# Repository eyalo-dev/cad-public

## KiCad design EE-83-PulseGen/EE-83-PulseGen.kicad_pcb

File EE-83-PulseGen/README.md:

Name:
- EE-83-PulseGen

Description:
- Pulse generator

Source reference:
- Everyday Electronics 1983-07 p.456 (58)

This is functional similar but not exact copy.
All dimension were estimated by eye.
Tried to use similar component placment as much as posible, but using only Kicad
standard PCB component footprint library, so dimentions may very.

PCB
- Done edit but
- Not tested

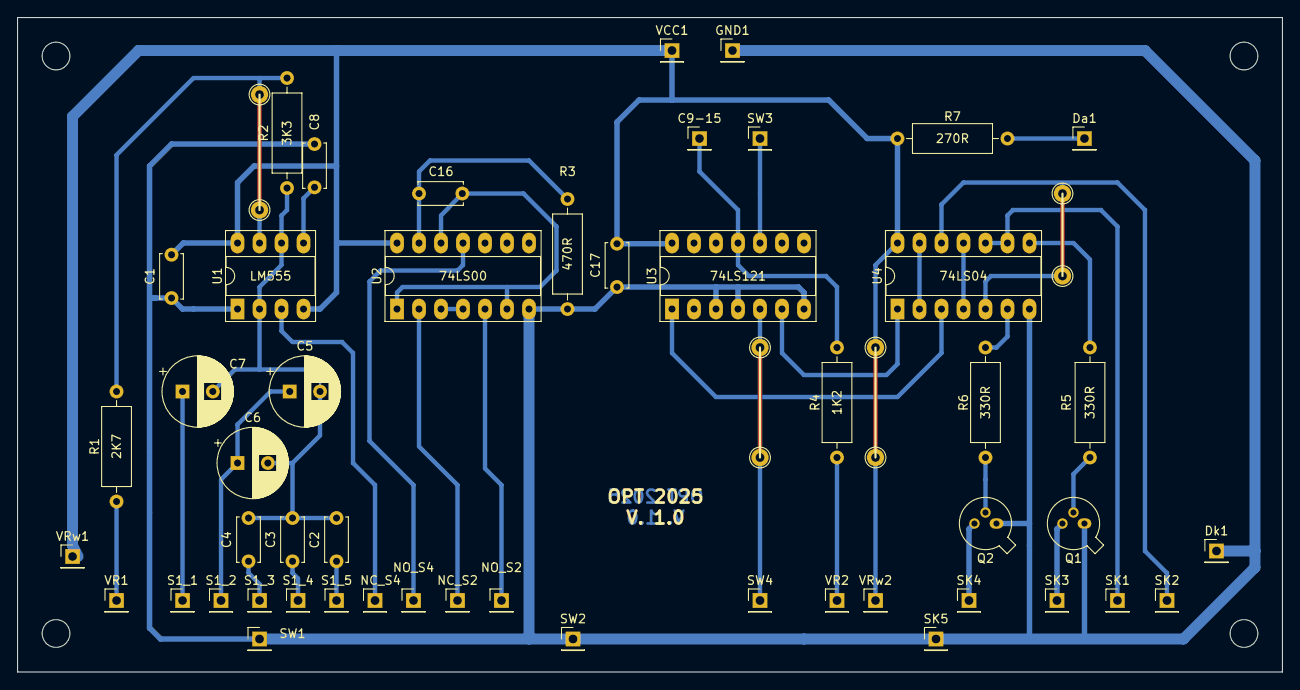
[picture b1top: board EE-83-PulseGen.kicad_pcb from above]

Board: 2 copper layers, 146.1 x 75.6 mm, 50 parts (0 on the bottom side), 35 nets.

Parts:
C1, C8, C17: 0.1uF; C_Disc_D5.0mm_W2.5mm_P5.00mm
C2, C16: 1nF; C_Disc_D5.0mm_W2.5mm_P5.00mm
C3: 15nF; C_Disc_D5.0mm_W2.5mm_P5.00mm
C4: 150nF; C_Disc_D5.0mm_W2.5mm_P5.00mm
C5: 1uF; CP_Radial_D8.0mm_P3.50mm
C6: 0.47uF; CP_Radial_D8.0mm_P3.50mm
C7: 15uF; CP_Radial_D8.0mm_P3.50mm
C9-15: PinHeader_1x01_P2.54mm_Vertical
Da1: PinHeader_1x01_P2.54mm_Vertical
Dk1: PinHeader_1x01_P2.54mm_Vertical
GND1: PinHeader_1x01_P2.54mm_Vertical
NC_S2, NC_S4: PinHeader_1x01_P2.54mm_Vertical
NO_S2, NO_S4: PinHeader_1x01_P2.54mm_Vertical
Q1, Q2: Q_NPN_EBC; TO-18-3
R1: 2K7; R_Axial_DIN0309_L9.0mm_D3.2mm_P12.70mm_Horizontal
R2: 3K3; R_Axial_DIN0309_L9.0mm_D3.2mm_P12.70mm_Horizontal
R3: 470R; R_Axial_DIN0309_L9.0mm_D3.2mm_P12.70mm_Horizontal
R4: 1K2; R_Axial_DIN0309_L9.0mm_D3.2mm_P12.70mm_Horizontal
R5, R6: 330R; R_Axial_DIN0309_L9.0mm_D3.2mm_P12.70mm_Horizontal
R7: 270R; R_Axial_DIN0309_L9.0mm_D3.2mm_P12.70mm_Horizontal
S1_1, S1_2, S1_3, S1_4, S1_5: PinHeader_1x01_P2.54mm_Vertical
SK1, SK2, SK3, SK4, SK5: PinHeader_1x01_P2.54mm_Vertical
SW1, SW2, SW3, SW4: PinHeader_1x01_P2.54mm_Vertical
U1: LM555; DIP-8_W7.62mm_Socket_LongPads
U2: 74LS00; DIP-14_W7.62mm_Socket_LongPads
U3: 74LS121; DIP-14_W7.62mm_Socket_LongPads
U4: 74LS04; DIP-14_W7.62mm_Socket_LongPads
VCC1: Conn_01x01_Female; PinHeader_1x01_P2.54mm_Vertical
VR1, VR2: PinHeader_1x01_P2.54mm_Vertical
VRw1, VRw2: PinHeader_1x01_P2.54mm_Vertical

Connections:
GNDREF: C1.1, C8.1, C17.1, Dk1.1, GND1.1, Q1.1, Q2.1, R3.1, SK5.1, SW1.1, SW2.1, U1.1, U2.7, U3.3, U3.4, U3.7, U4.7
unnamed: C2.1, C3.1, C4.1, C5.2, C6.2, C7.2, R2.1, U1.2, U1.6
unnamed: C2.2, S1_5.1
unnamed: C3.2, S1_4.1
unnamed: C4.2, S1_3.1
unnamed: C5.1, C6.1, S1_2.1
unnamed: C7.1, S1_1.1
unnamed: C8.2, U1.5
unnamed: C9-15.1, R4.1, U3.11
unnamed: C16.1, R3.2, U2.13
unnamed: C16.2, U2.1, U2.6, U2.12
unnamed: Da1.1, R7.1
unnamed: NC_S2.1, U2.2
unnamed: NC_S4.1, U1.3
unnamed: NO_S2.1, U2.5
unnamed: NO_S4.1, U2.11
unnamed: Q1.2, R5.1
unnamed: Q1.3, SK3.1
unnamed: Q2.2, R6.2
unnamed: Q2.3, SK4.1
unnamed: R1.1, R2.2, U1.7
unnamed: R1.2, VR1.1
unnamed: R4.2, VR2.1
unnamed: R5.2, U4.8
unnamed: R6.1, U4.6
unnamed: SW4.1, U3.5
unnamed: SK1.1, U4.9, U4.10
unnamed: SK2.1, U4.5, U4.12
unnamed: SW3.1, U3.10
unnamed: U2.3, U2.4
unnamed: U3.1, U4.3
unnamed: U3.6, U4.1
unnamed: U4.4, U4.11
unnamed: U4.2, U4.13
VCC: C1.2, C17.2, R7.2, U1.4, U1.8, U2.14, U3.14, U4.14, VCC1.1, VRw1.1, VRw2.1

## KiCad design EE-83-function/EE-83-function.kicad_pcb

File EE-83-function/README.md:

Name:
- EE-83-function

Description:
- Function generator

Source reference:
- Everyday Electronics 1983-04 p.14 (205)

This is functional similar but not exact copy.
All dimension were estimated by eye.
Tried to use similar component placment as much as posible, but using only Kicad
standard PCB component footprint library, so dimentions may very.

PCB
- Done edit but
- Not tested

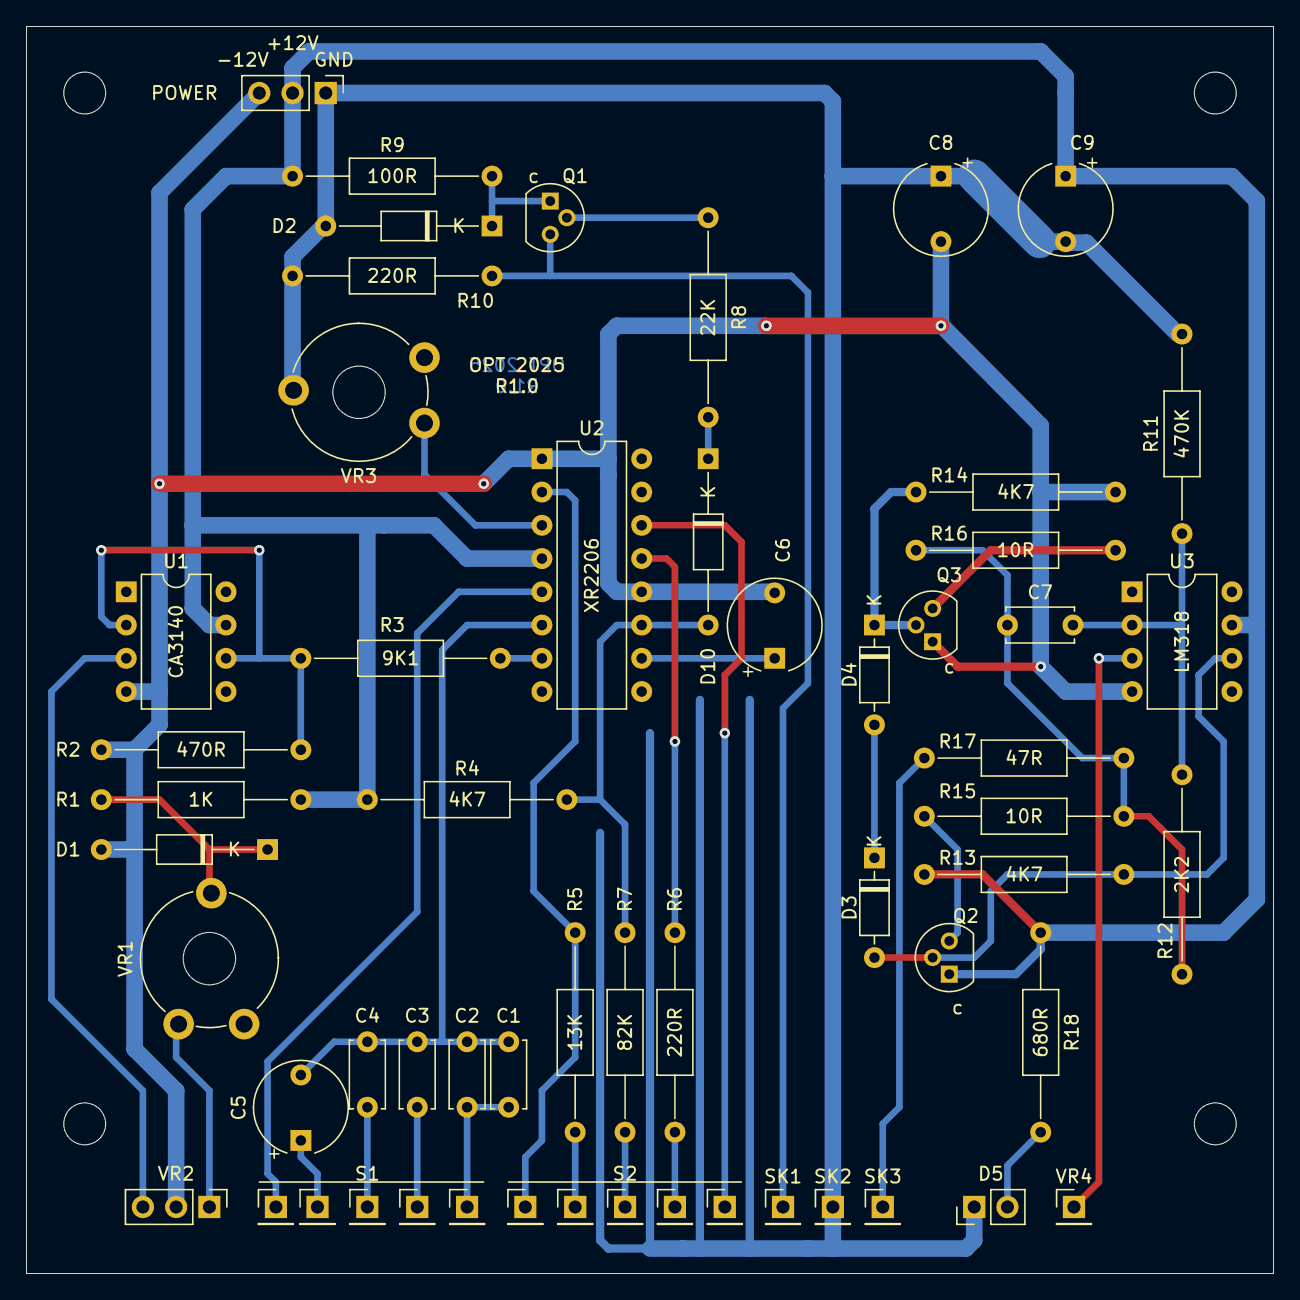
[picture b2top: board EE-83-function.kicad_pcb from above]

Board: 2 copper layers, 95.2 x 95.2 mm, 57 parts (0 on the bottom side), 37 nets.

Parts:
C1: 82p; C_Disc_D5.0mm_W2.5mm_P5.00mm
C2: 820p; C_Disc_D5.0mm_W2.5mm_P5.00mm
C3: 10n; C_Disc_D5.0mm_W2.5mm_P5.00mm
C4: 100n; C_Disc_D5.0mm_W2.5mm_P5.00mm
C5: 1u; CP_Radial_Tantal_D7.0mm_P5.00mm
C6, C8, C9: 22u; CP_Radial_Tantal_D7.0mm_P5.00mm
C7: 56p; C_Disc_D5.0mm_W2.5mm_P5.00mm
D1, D2, D10: D_DO-35_SOD27_P12.70mm_Horizontal
D3, D4: 1N4148; D_DO-35_SOD27_P7.62mm_Horizontal
D5: LED; PinHeader_1x02_P2.54mm_Vertical
POWER: 1K; PinHeader_1x03_P2.54mm_Vertical
Q1: BSX 20; TO-92
Q2: BC338; TO-92
Q3: BC328; TO-92
R1: 1K; R_Axial_DIN0207_L6.3mm_D2.5mm_P15.24mm_Horizontal
R2: 470R; R_Axial_DIN0207_L6.3mm_D2.5mm_P15.24mm_Horizontal
R3: 9K1; R_Axial_DIN0207_L6.3mm_D2.5mm_P15.24mm_Horizontal
R4, R13, R14: 4K7; R_Axial_DIN0207_L6.3mm_D2.5mm_P15.24mm_Horizontal
R5: 13K; R_Axial_DIN0207_L6.3mm_D2.5mm_P15.24mm_Horizontal
R6, R10: 220R; R_Axial_DIN0207_L6.3mm_D2.5mm_P15.24mm_Horizontal
R7: 82K; R_Axial_DIN0207_L6.3mm_D2.5mm_P15.24mm_Horizontal
R8: 22K; R_Axial_DIN0207_L6.3mm_D2.5mm_P15.24mm_Horizontal
R9: 100R; R_Axial_DIN0207_L6.3mm_D2.5mm_P15.24mm_Horizontal
R11: 470K; R_Axial_DIN0207_L6.3mm_D2.5mm_P15.24mm_Horizontal
R12: 2K2; R_Axial_DIN0207_L6.3mm_D2.5mm_P15.24mm_Horizontal
R15, R16: 10R; R_Axial_DIN0207_L6.3mm_D2.5mm_P15.24mm_Horizontal
R17: 47R; R_Axial_DIN0207_L6.3mm_D2.5mm_P15.24mm_Horizontal
R18: 680R; R_Axial_DIN0207_L6.3mm_D2.5mm_P15.24mm_Horizontal
S1, S2: Conn_01x01_Female; PinHeader_1x01_P2.54mm_Vertical
SK1, SK1#2, SK1#3, SK1#4, SK1#5, SK1#6, SK1#7, SK1#8, SK1#9, SK2, SK3: Conn_01x01_Female; PinHeader_1x01_P2.54mm_Vertical
U1: CA3140; DIP-8_W7.62mm
U2: XR2206; DIP-16_W7.62mm
U3: LM318; DIP-8_W7.62mm
VR1: 2K2; Potentiometer_Piher_PT-10-V10_Vertical_Hole
VR2: 1K; PinHeader_1x03_P2.54mm_Vertical
VR3: 47K; Potentiometer_Piher_PT-10-V10_Vertical_Hole
VR4: Conn_01x01_Female; PinHeader_1x01_P2.54mm_Vertical

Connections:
+12V: C9.1, POWER.2, Q2.1, R1.1, R4.1, R9.1, R13.1, R18.1, U1.7, U2.4, U3.7
-12V: C6.2, C8.2, D1.2, POWER.3, Q3.1, R2.1, R14.2, U1.4, U2.1, U2.12, U3.4, VR2.2
GND: C8.1, C9.2, D2.2, D5.1, POWER.1, R10.2, R11.2, SK2.1, VR3.2
unnamed: C1.1, C2.1, SK1#4.1
unnamed: C1.2, C2.2, C3.2, C4.2, C5.2, U2.6
unnamed: C3.1, SK1#3.1
unnamed: C4.1, S1.1
unnamed: C5.1, SK1#2.1
unnamed: C6.1, U2.10
unnamed: C7.1, R12.1, R15.2, R16.1, R17.2
unnamed: C7.2, R11.1, R12.2, U3.2
unnamed: D1.1, R1.2, VR1.1, VR1.2
unnamed: D2.1, Q1.1, R9.2
unnamed: D3.1, D4.2
unnamed: D3.2, Q2.2, R13.2, U3.6
unnamed: D4.1, Q3.2, R14.1
unnamed: D5.2, R18.2
unnamed: D10.1, R4.2, R7.2, U2.11
unnamed: D10.2, R8.2
unnamed: Q1.2, R8.1
unnamed: Q1.3, R10.1, SK1#9.1
unnamed: Q2.3, R15.1
unnamed: Q3.3, R16.2
unnamed: R2.2, R3.2, U1.2, U1.6
unnamed: R3.1, U2.7
unnamed: R5.1, SK1#7.1
unnamed: R5.2, SK1#8.1, U2.2
unnamed: R6.1, SK1#6.1
unnamed: R6.2, U2.13
unnamed: R7.1, S2.1
unnamed: R17.1, SK3.1
unnamed: SK1.1, U2.5
unnamed: SK1#5.1, U2.14
unnamed: U1.3, VR2.3
unnamed: U2.3, VR3.3
unnamed: U3.3, VR4.1
unnamed: VR1.3, VR2.1

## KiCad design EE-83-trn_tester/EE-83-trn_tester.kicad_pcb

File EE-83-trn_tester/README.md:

Name:
- EE-83-trn_tester

Description:
- Transistor and Diode Tester

Source reference:
- Everyday Electronics 1983-06 p.370 (44)

This is functional similar but not exact copy.
All dimension were estimated by eye.
Tried to use similar component placment as much as posible, but using only Kicad
standard PCB component footprint library, so dimentions may very.

Need to verify measurement of meter contacts for vertical mounting, like artical.

Two versions:
- 1 my failed attempt to make PCB width smaller - fit within the 100mm X 100mm limit.
- 2 this is sized similar to original. 

PCB
- Done edit but
- Not tested

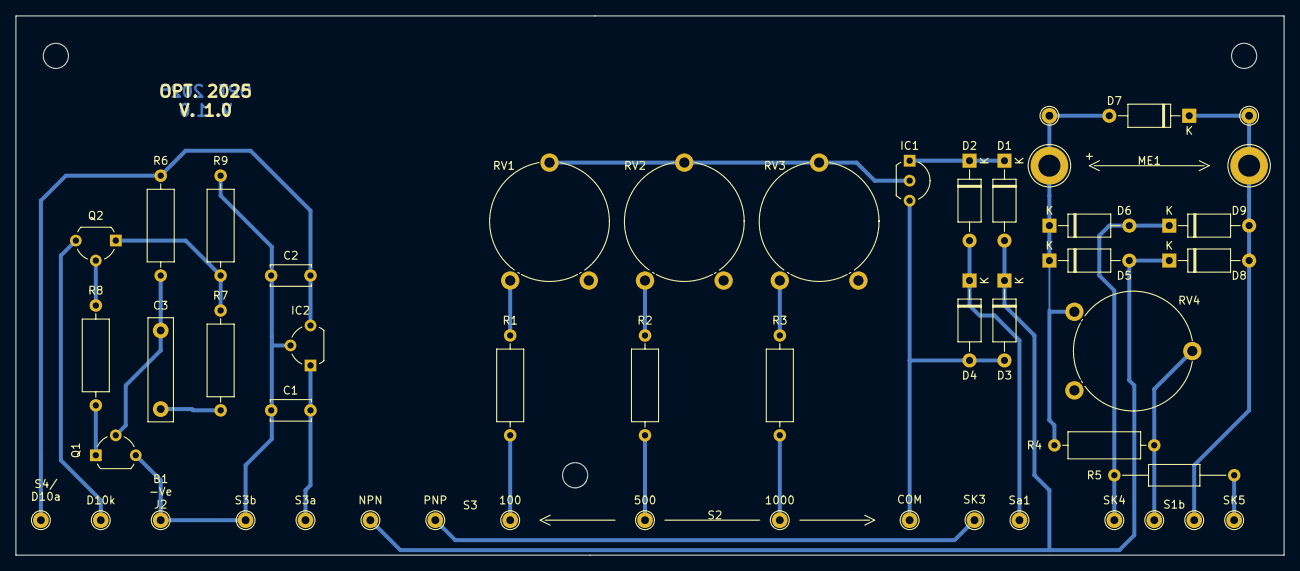
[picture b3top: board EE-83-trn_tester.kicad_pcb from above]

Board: 2 copper layers, 161.3 x 68.6 mm, 44 parts (0 on the bottom side), 21 nets.

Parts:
100, 500, 1000: TestPoint_THTPad_D2.0mm_Drill1.0mm
C1, C2: 100nF; C_Disc_D5.0mm_W2.5mm_P5.00mm
C3: 330nF; C_Rect_L13.0mm_W3.0mm_P10.00mm_FKS3_FKP3_MKS4
COM: TestPoint_THTPad_D2.0mm_Drill1.0mm
D1, D2, D3, D4, D5, D6, D7, D8, D9: 1n4148; D_A-405_P10.16mm_Horizontal
D10k: TestPoint_THTPad_D2.0mm_Drill1.0mm
IC1: LM334Z; TO-92L_Inline_Wide
IC2: uA7805; TO-92L_Wide
J2: -Ve; TestPoint_THTPad_D2.0mm_Drill1.0mm
NPN: TestPoint_THTPad_D2.0mm_Drill1.0mm
PNP: TestPoint_THTPad_D2.0mm_Drill1.0mm
Q1: BC108C; TO-92L_Wide
Q2: BC309; TO-92L_Wide
R1: 620R; R_Axial_DIN0309_L9.0mm_D3.2mm_P12.70mm_Horizontal
R2: 3K; R_Axial_DIN0309_L9.0mm_D3.2mm_P12.70mm_Horizontal
R3: 6K2; R_Axial_DIN0309_L9.0mm_D3.2mm_P12.70mm_Horizontal
R4: 39R; R_Axial_DIN0309_L9.0mm_D3.2mm_P12.70mm_Horizontal
R5: 560R; R_Axial_DIN0207_L6.3mm_D2.5mm_P15.24mm_Horizontal
R6: 3M3; R_Axial_DIN0309_L9.0mm_D3.2mm_P12.70mm_Horizontal
R7: 3K3; R_Axial_DIN0309_L9.0mm_D3.2mm_P12.70mm_Horizontal
R8: 1K; R_Axial_DIN0309_L9.0mm_D3.2mm_P12.70mm_Horizontal
R9: 100R; R_Axial_DIN0309_L9.0mm_D3.2mm_P12.70mm_Horizontal
RV1: 100R; Potentiometer_Piher_PT-15-V15_Vertical
RV2: 470R; Potentiometer_Piher_PT-15-V15_Vertical
RV3, RV4: 1K; Potentiometer_Piher_PT-15-V15_Vertical
S1b, S3a, S3b: TestPoint_THTPad_D2.0mm_Drill1.0mm
SK3: TestPoint_THTPad_D2.0mm_Drill1.0mm
SK4: c; TestPoint_THTPad_D2.0mm_Drill1.0mm
SK5: k; TestPoint_THTPad_D2.0mm_Drill1.0mm
Sa1: TestPoint_THTPad_D2.0mm_Drill1.0mm

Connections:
unnamed: C1.1, IC2.3, S3a.1
unnamed: C1.2, C2.2, IC2.2, J2.1, Q1.3, R9.1, S3b.1
unnamed: C2.1, IC2.1, R6.2
unnamed: C3.1, Q1.2, R6.1
unnamed: C3.2, R7.1
unnamed: D1.1, D2.1, IC1.1
unnamed: D1.2, D3.1, D5.2, D8.1, NPN.1
unnamed: D2.2, D4.1, Sa1.1
unnamed: COM.1, D3.2, D4.2, IC1.3
unnamed: D5.1, D6.1, D7.2, R4.2, RV4.3
unnamed: D6.2, D9.1, R5.1, SK4.1
unnamed: D7.1, D8.2, D9.2, S1b.1
unnamed: IC1.2, RV1.2, RV2.2, RV3.2
unnamed: Q1.1, R8.2
unnamed: Q2.1, R7.2, R9.2
unnamed: Q2.2, R8.1
unnamed: R1.1, RV1.3
unnamed: R2.1, RV2.3
unnamed: R3.1, RV3.3
unnamed: R4.1, RV4.2
unnamed: R5.2, SK5.1

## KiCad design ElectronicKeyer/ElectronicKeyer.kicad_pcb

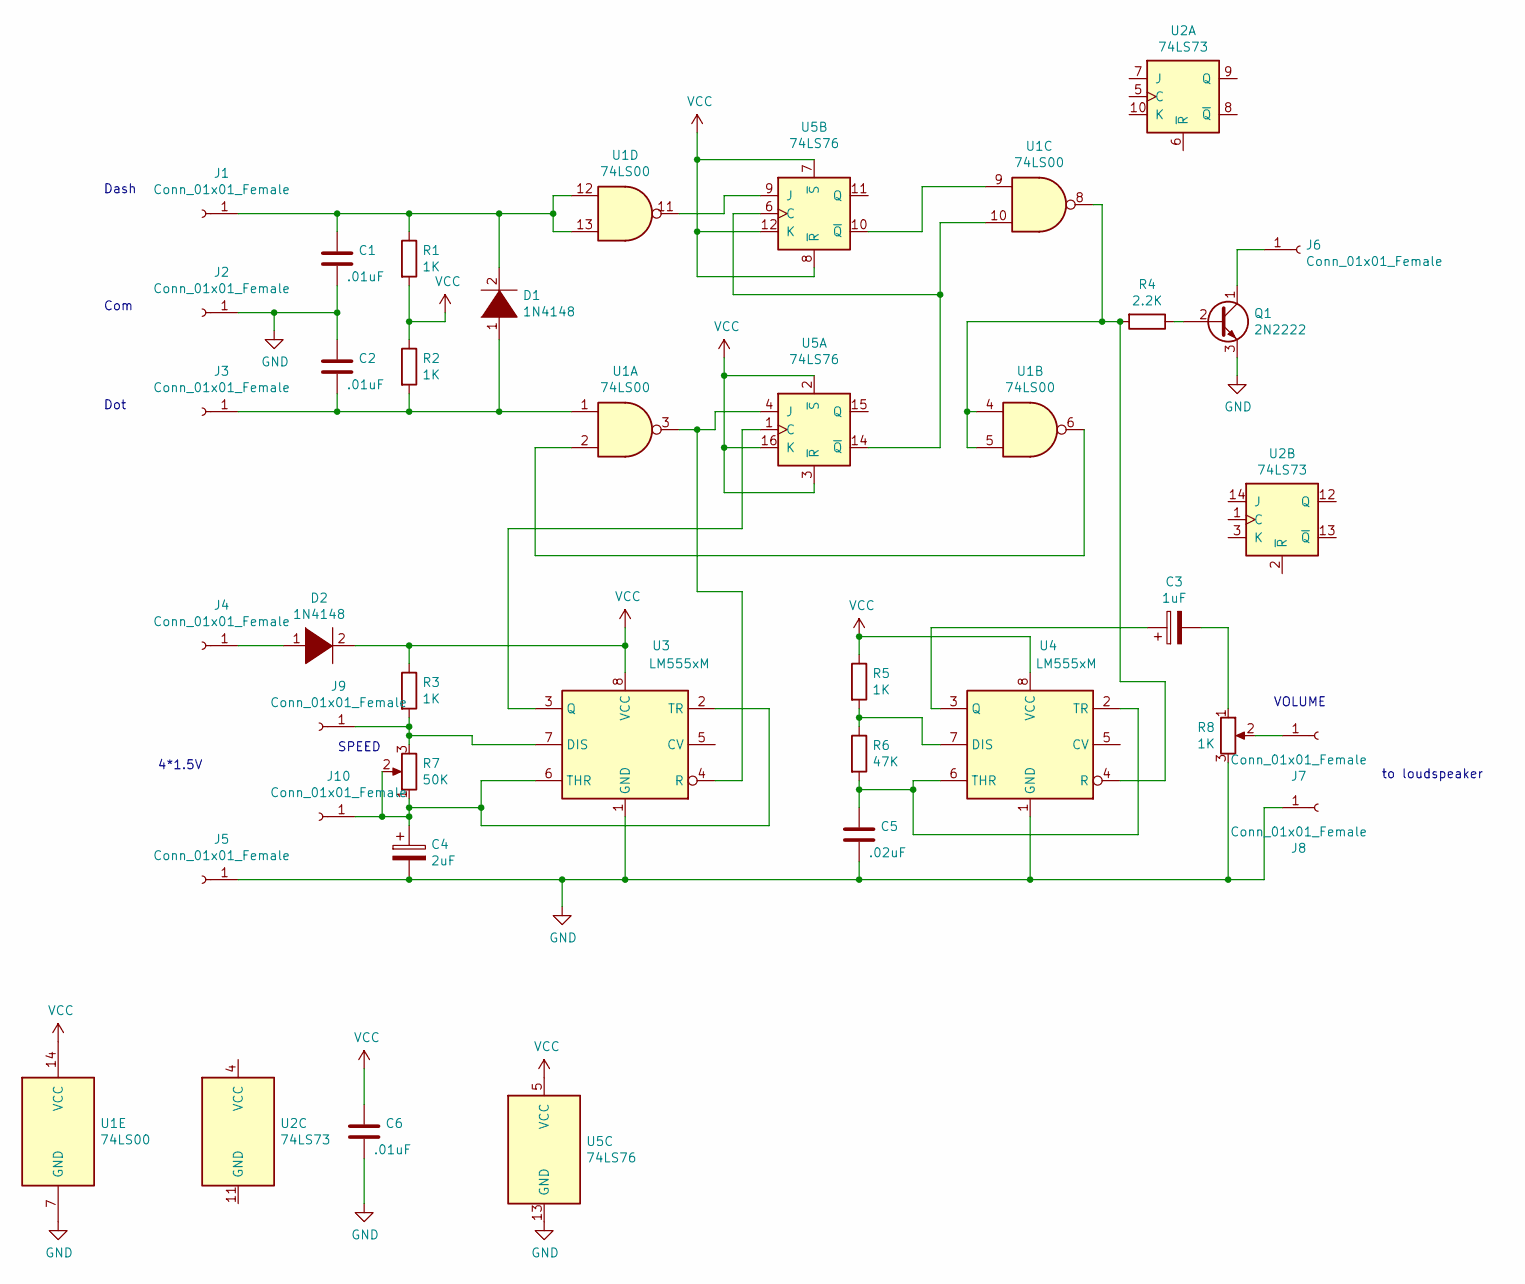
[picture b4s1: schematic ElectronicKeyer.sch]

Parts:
C1, C2, C6: .01uF; C_Disc_D5.0mm_W2.5mm_P5.00mm
C3: 1uF; CP_Radial_D5.0mm_P2.50mm
C4: 2uF; CP_Radial_D5.0mm_P2.50mm
C5: .02uF; C_Disc_D5.0mm_W2.5mm_P5.00mm
D1, D2: 1N4148; D_DO-35_SOD27_P7.62mm_Horizontal
J1, J2, J3, J4, J5, J6, J7, J8, J9, J10: Conn_01x01_Female; PinHeader_1x01_P2.54mm_Vertical
Q1: 2N2222; TO-18-3
R1, R2, R3, R5: 1K; R_Axial_DIN0207_L6.3mm_D2.5mm_P15.24mm_Horizontal
R4: 2.2K; R_Axial_DIN0207_L6.3mm_D2.5mm_P15.24mm_Horizontal
R6: 47K; R_Axial_DIN0207_L6.3mm_D2.5mm_P15.24mm_Horizontal
R7: 50K
R8: 1K
U1: 74LS00; DIP-14_W7.62mm_Socket_LongPads
U2: 74LS73
U3, U4: LM555xM; DIP-8_W7.62mm_Socket_LongPads
U5: 74LS76; DIP-16_W7.62mm_Socket_LongPads

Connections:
GND: C1.2, C2.1, C4.2, C5.2, C6.2, J2.1, J5.1, J8.1, Q1.3 (E), R8.3, U1.7 (GND), U3.1 (GND), U4.1 (GND), U5.13 (GND)
unnamed: C1.1, D1.2 (A), J1.1, R1.1, U1.12, U1.13
unnamed: C2.2, D1.1 (K), J3.1, R2.2, U1.1
unnamed: C3.1, U4.3 (Q)
unnamed: C3.2, J7.1, R8.1, R8.2
unnamed: C4.1, J10.1, R7.1, R7.2, U3.2 (TR), U3.6 (THR)
unnamed: C5.1, R6.2, U4.2 (TR), U4.6 (THR)
unnamed: D2.1 (K), J4.1
unnamed: J6.1, Q1.1 (C)
unnamed: J9.1, R3.2, R7.3, U3.7 (DIS)
unnamed: Q1.2 (B), R4.1
unnamed: R4.2, U1.4, U1.5, U1.8, U4.4 (R)
unnamed: R5.2, R6.1, U4.7 (DIS)
unnamed: U1.2, U1.6
unnamed: U1.3, U3.4 (R), U5.4 (J)
unnamed: U1.9, U5.10 (~Q)
unnamed: U1.10, U5.6 (C), U5.14 (~Q)
unnamed: U1.11, U5.9 (J)
unnamed: U3.3 (Q), U5.1 (C)
VCC: C6.1, D2.2 (A), R1.2, R2.1, R3.1, R5.1, U1.14 (VCC), U3.8 (VCC), U4.8 (VCC), U5.2 (~S), U5.3 (~R), U5.5 (VCC), U5.7 (~S), U5.8 (~R), U5.12 (K), U5.16 (K)

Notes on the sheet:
Dash
Dot
Com
4*1.5V
to loudspeaker
SPEED
VOLUME

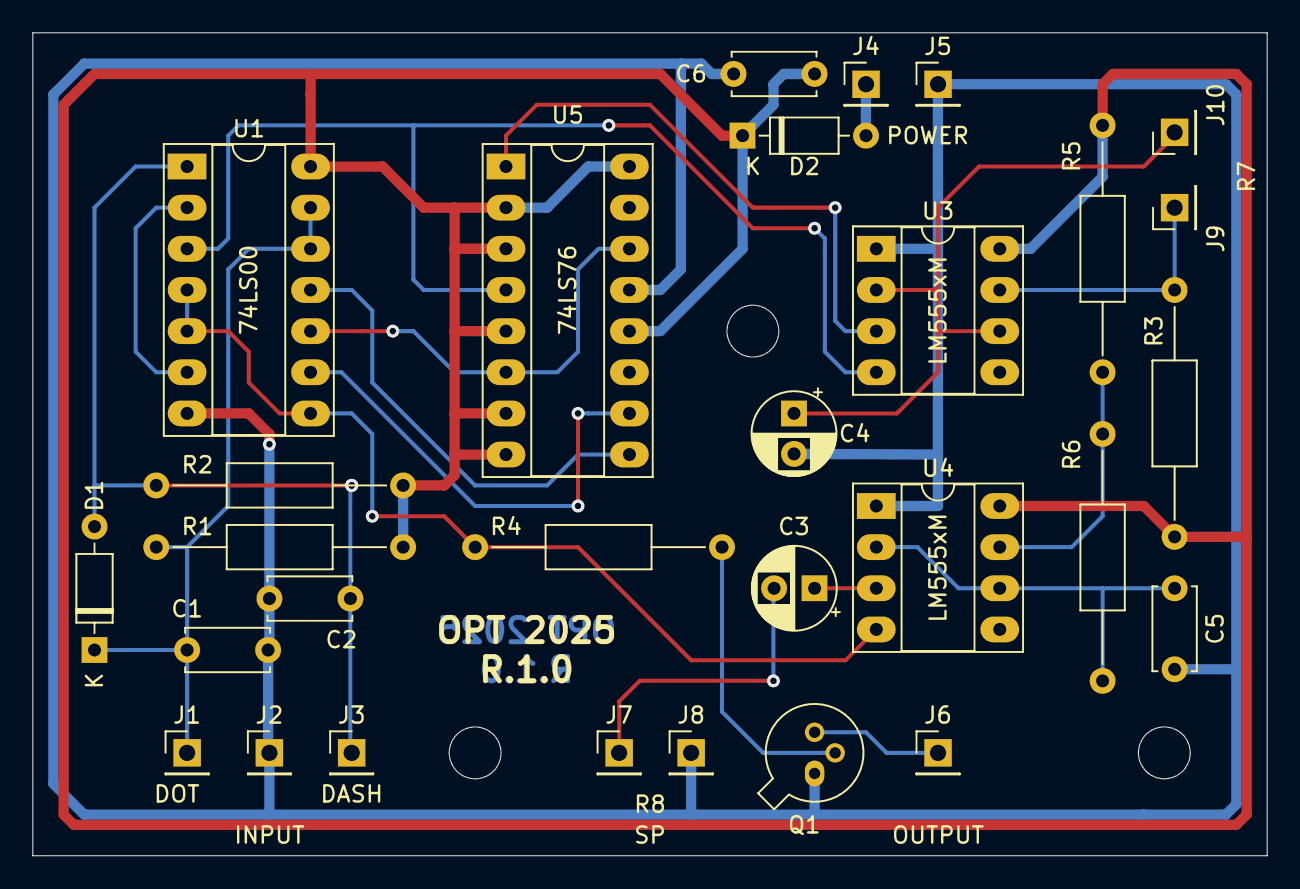
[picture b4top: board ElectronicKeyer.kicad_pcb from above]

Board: 2 copper layers, 76.2 x 50.8 mm, 29 parts (0 on the bottom side), 20 nets.

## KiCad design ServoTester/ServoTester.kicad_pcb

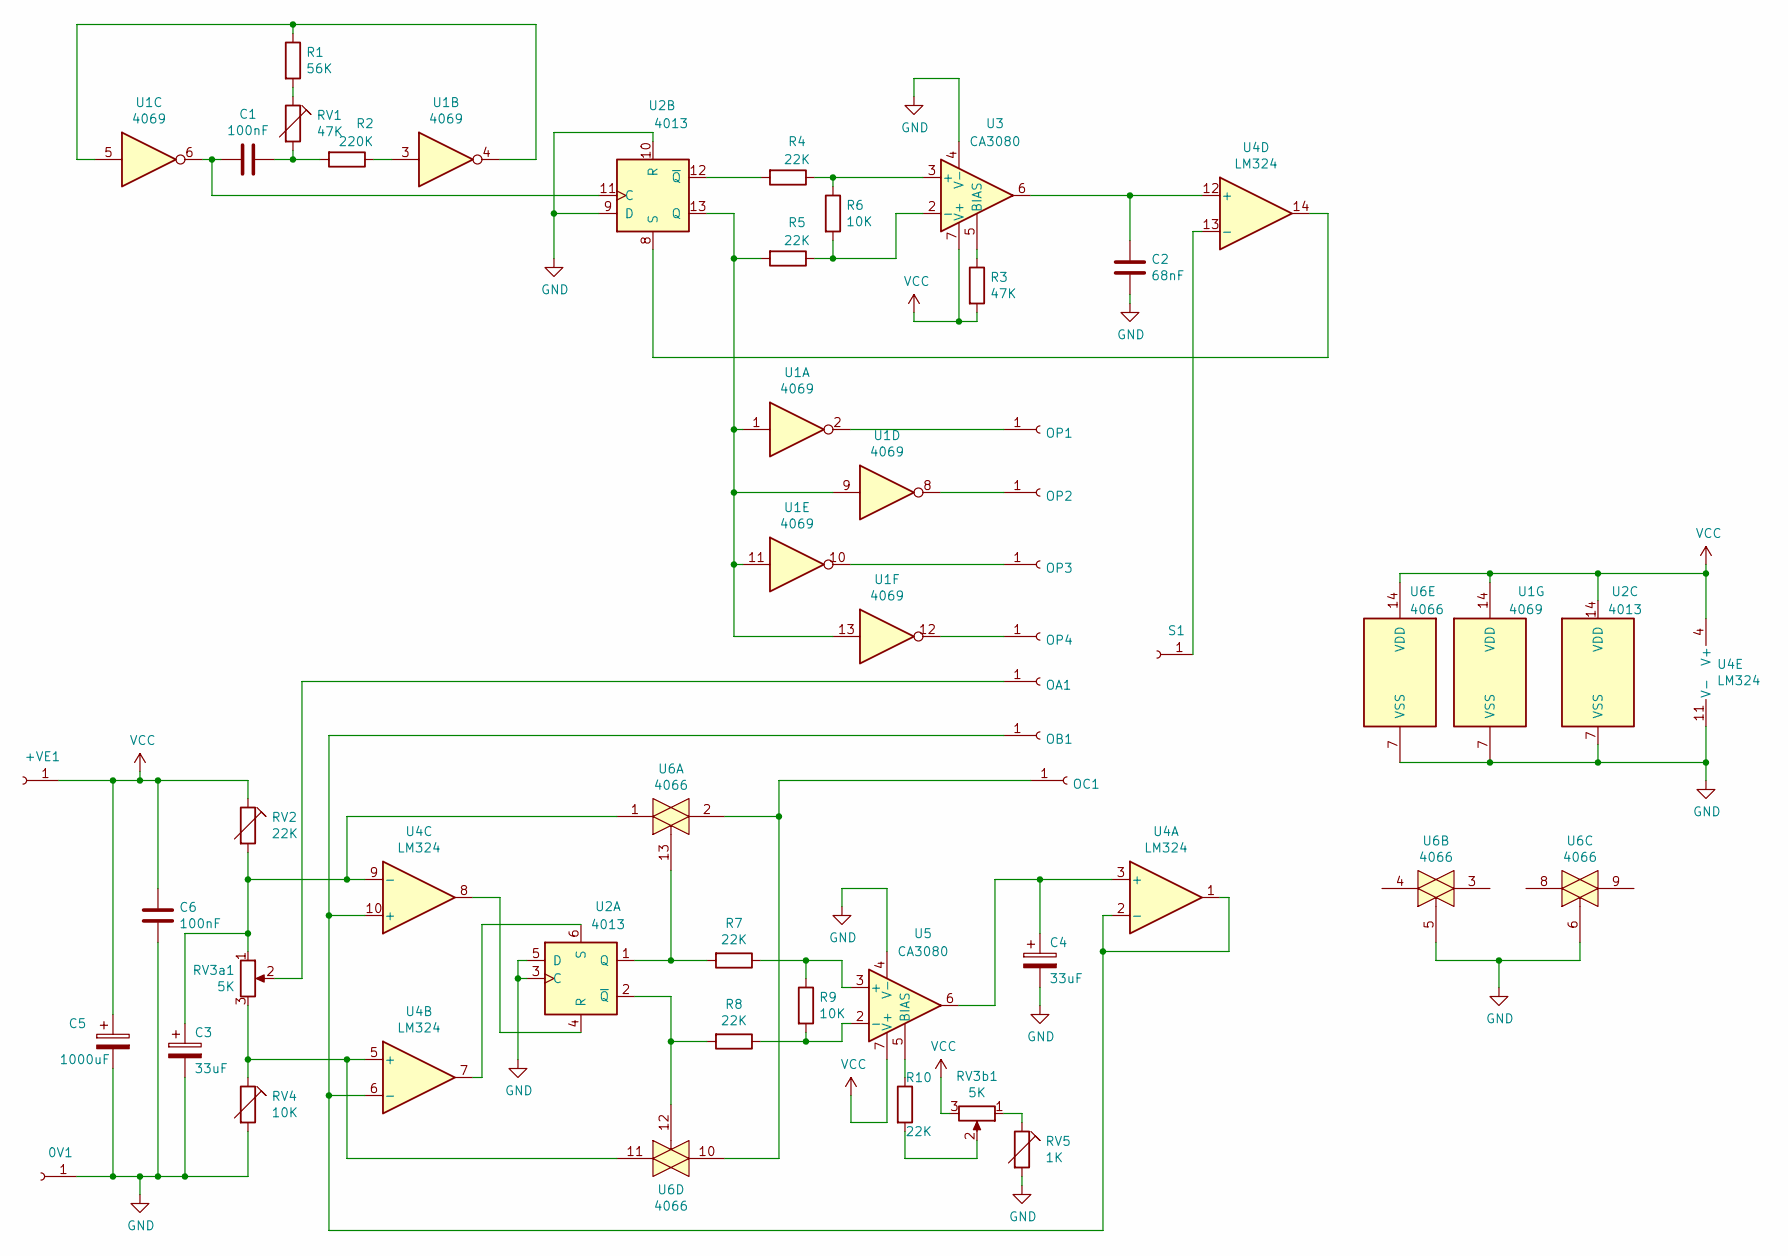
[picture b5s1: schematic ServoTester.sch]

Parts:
0V1: Conn_01x01_Female; TestPoint_THTPad_D2.0mm_Drill1.0mm
+VE1: Conn_01x01_Female; TestPoint_THTPad_D2.0mm_Drill1.0mm
C1, C6: 100nF; C_Rect_L9.0mm_W2.7mm_P7.50mm_MKT
C2: 68nF; C_Rect_L9.0mm_W2.7mm_P7.50mm_MKT
C3, C4: 33uF; CP_Radial_Tantal_D7.0mm_P5.00mm
C5: 1000uF; CP_Axial_L20.0mm_D10.0mm_P26.00mm_Horizontal
OA1: Conn_01x01_Female; TestPoint_THTPad_D2.0mm_Drill1.0mm
OB1: Conn_01x01_Female; TestPoint_THTPad_D2.0mm_Drill1.0mm
OC1: Conn_01x01_Female; TestPoint_THTPad_D2.0mm_Drill1.0mm
OP1, OP2, OP3, OP4: Conn_01x01_Female; TestPoint_THTPad_D2.0mm_Drill1.0mm
R1: 56K; R_Axial_DIN0207_L6.3mm_D2.5mm_P10.16mm_Horizontal
R2: 220K; R_Axial_DIN0207_L6.3mm_D2.5mm_P10.16mm_Horizontal
R3: 47K; R_Axial_DIN0207_L6.3mm_D2.5mm_P10.16mm_Horizontal
R4, R5, R7, R8, R10: 22K; R_Axial_DIN0207_L6.3mm_D2.5mm_P10.16mm_Horizontal
R6, R9: 10K; R_Axial_DIN0207_L6.3mm_D2.5mm_P10.16mm_Horizontal
RV1: 47K; Potentiometer_Piher_PT-15-V02_Vertical
RV2: 22K; Potentiometer_Piher_PT-15-V02_Vertical
RV3a1, RV3b1: 5K
RV4: 10K; Potentiometer_Piher_PT-15-V02_Vertical
RV5: 1K; Potentiometer_Piher_PT-15-V02_Vertical
S1: Conn_01x01_Female; TestPoint_THTPad_D2.0mm_Drill1.0mm
U1: 4069; DIP-14_W7.62mm_Socket_LongPads
U2: 4013; DIP-14_W7.62mm_Socket_LongPads
U3, U5: CA3080; DIP-8_W7.62mm_Socket_LongPads
U4: LM324; DIP-14_W7.62mm_Socket_LongPads
U6: 4066; DIP-14_W7.62mm_Socket_LongPads

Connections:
GND: 0V1.1, C2.2, C3.2, C4.2, C5.2, C6.2, RV3b1.1, RV4.2, RV4.3, RV5.1, RV5.2, U1.7 (VSS), U2.3 (C), U2.5 (D), U2.7 (VSS), U2.9 (D), U2.10 (R), U3.4 (V-), U4.11 (V-), U5.4 (V-), U6.5, U6.6, U6.7 (VSS)
unnamed: C1.1, R2.2, RV1.2, RV1.3
unnamed: C1.2, U1.6, U2.11 (C)
unnamed: C2.1, U3.6, U4.12 (+)
unnamed 4: C3.1, RV2.2, RV3a1.1, U4.9 (-), U6.1; also elsewhere on the board
unnamed: C4.1, U4.3 (+), U5.6
unnamed: OB1.1, U4.1, U4.2 (-), U4.6 (-), U4.10 (+)
unnamed: OC1.1, U6.2, U6.10
unnamed: OP1.1, U1.2
unnamed: OP2.1, U1.8
unnamed: OP3.1, U1.10
unnamed: OP4.1, U1.12
unnamed: R1.1, U1.4, U1.5
unnamed: R1.2, RV1.1
unnamed: R2.1, U1.3
unnamed: R3.1, U3.5 (BIAS)
unnamed: R4.1, R6.1, U3.3 (+)
unnamed: R4.2, U2.12 (~Q)
unnamed: R5.1, R6.2, U3.2 (-)
unnamed: R5.2, U1.1, U1.9, U1.11, U1.13, U2.13 (Q)
unnamed: R7.1, R9.1, U5.3 (+)
unnamed: R7.2, U2.1 (Q), U6.13
unnamed: R8.1, R9.2, U5.2 (-)
unnamed: R8.2, U2.2 (~Q), U6.12
unnamed: R10.1, U5.5 (BIAS)
unnamed: OA1.1, RV3a1.2
unnamed 26: RV3a1.3, RV4.1, U4.5 (+), U6.11; also elsewhere on the board
unnamed: R10.2, RV3b1.2
unnamed: S1.1, U4.13 (-)
unnamed: U2.4 (R), U4.8
unnamed: U2.6 (S), U4.7
unnamed: U2.8 (S), U4.14
VCC: +VE1.1, C5.1, C6.1, R3.2, RV2.1, RV3b1.3, U1.14 (VDD), U2.14 (VDD), U3.7 (V+), U4.4 (V+), U5.7 (V+), U6.14 (VDD); also elsewhere on the board

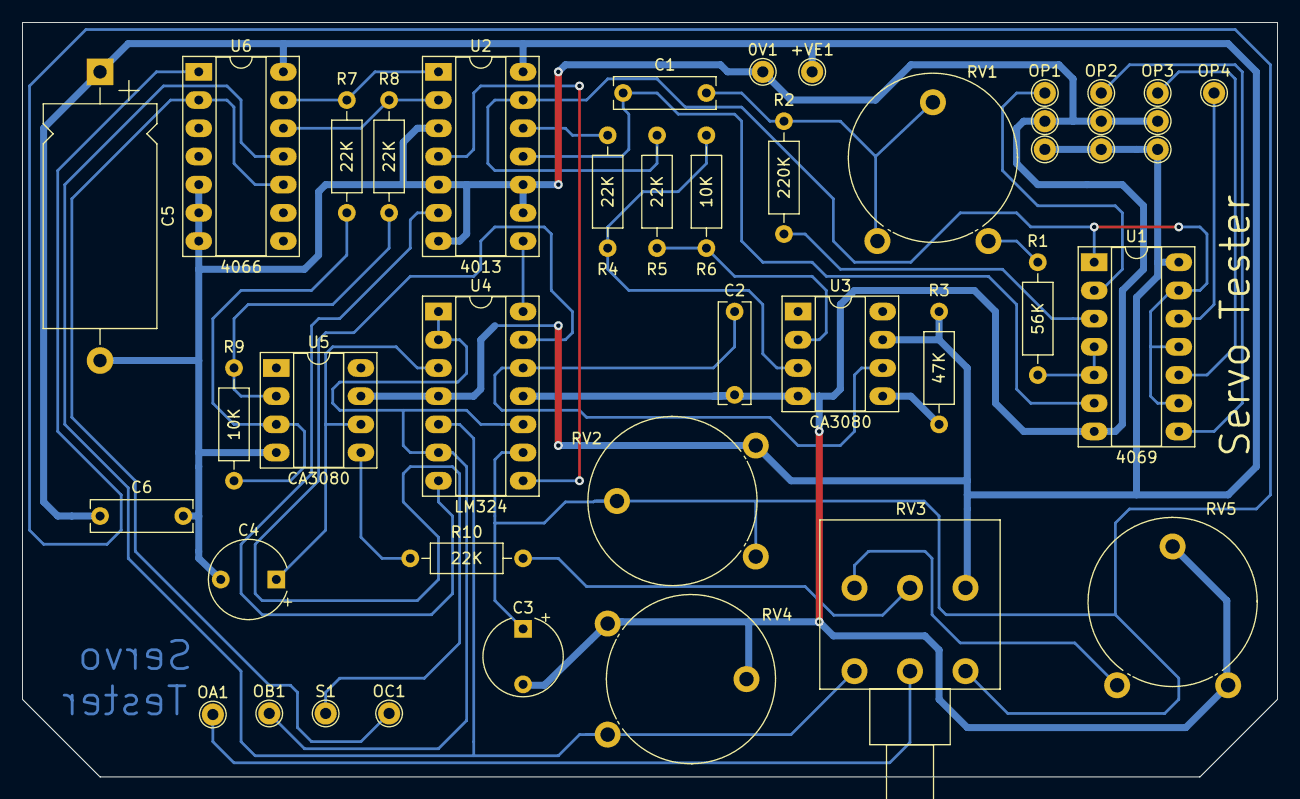
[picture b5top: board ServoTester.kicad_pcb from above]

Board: 2 copper layers, 113.0 x 67.9 mm, 37 parts (0 on the bottom side), 31 nets.

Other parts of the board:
RV3: Potentiometer_Piher_T-16H_Double_Horizontal

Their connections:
unnamed 4: RV3.3; also elsewhere on the board
unnamed 26: RV3.1; also elsewhere on the board
VCC: RV3.6; also elsewhere on the board
